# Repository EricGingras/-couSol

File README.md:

# Écou-Terre

**Déscription du projet:** Nous sommes en train de concevoir un module qui peut capter les bruits émis par les vers de terre, offrant ainsi une perspective sur la biodiversité et la santé des sols.  Ceci est le répertoire git de tous les fichiers techniques pour notre projet.

**Déscription technique:** Nous utilisons un microphone électret pour capter le bruit des vers de terre. Ce signal est ensuite amplifié et numérisé pour pouvoir le transmettre dans un ESP-32 en format I2S. Par la suite, ces données I2S sont enregistrées dans une carte SD en format WAV, ce qui permet ensuite de les écouter sur un ordinateur. Il y a aussi un connecteur jack 3,5mm pour l'écoute en temps réelle des vers de terre. Éventuellement, nous souhaitons ajouter un module GPS pouvant indiquer la position géographique de tous les échantillons sonores prélevés. Le module au complet est alimenté par une pile 4.2 volts. Pour le contrôler, nous allons avoir un page web avec un interface pour le démarrage, l'ârret et d'autre fonctions du module.

# Fichiers
> Déscription des fichiers dans le répertoire git.
- **3d_print:** Contient les fichiers pour la seule impression 3d que nous avons fait pour notre projet à date: une base pour le boîtier.
- **Documentation_pieces:** Contient tous les fichiers de documentation pour les pièces principales qui se retrouvent sur le module.
- **Documentation_session5:** Contient des fichiers de la session passée qui servent encore pour notre projet.
- **Fichier_PCB:** Contient tous les fichiers KiCad pour les PCB.
- **Prog_ESP-32:** Contient le code pour l'enregistrement des données I2S qui utilisait ESP-IDF ainsi que le code pour le serveur web qui servira à contrôler le module.

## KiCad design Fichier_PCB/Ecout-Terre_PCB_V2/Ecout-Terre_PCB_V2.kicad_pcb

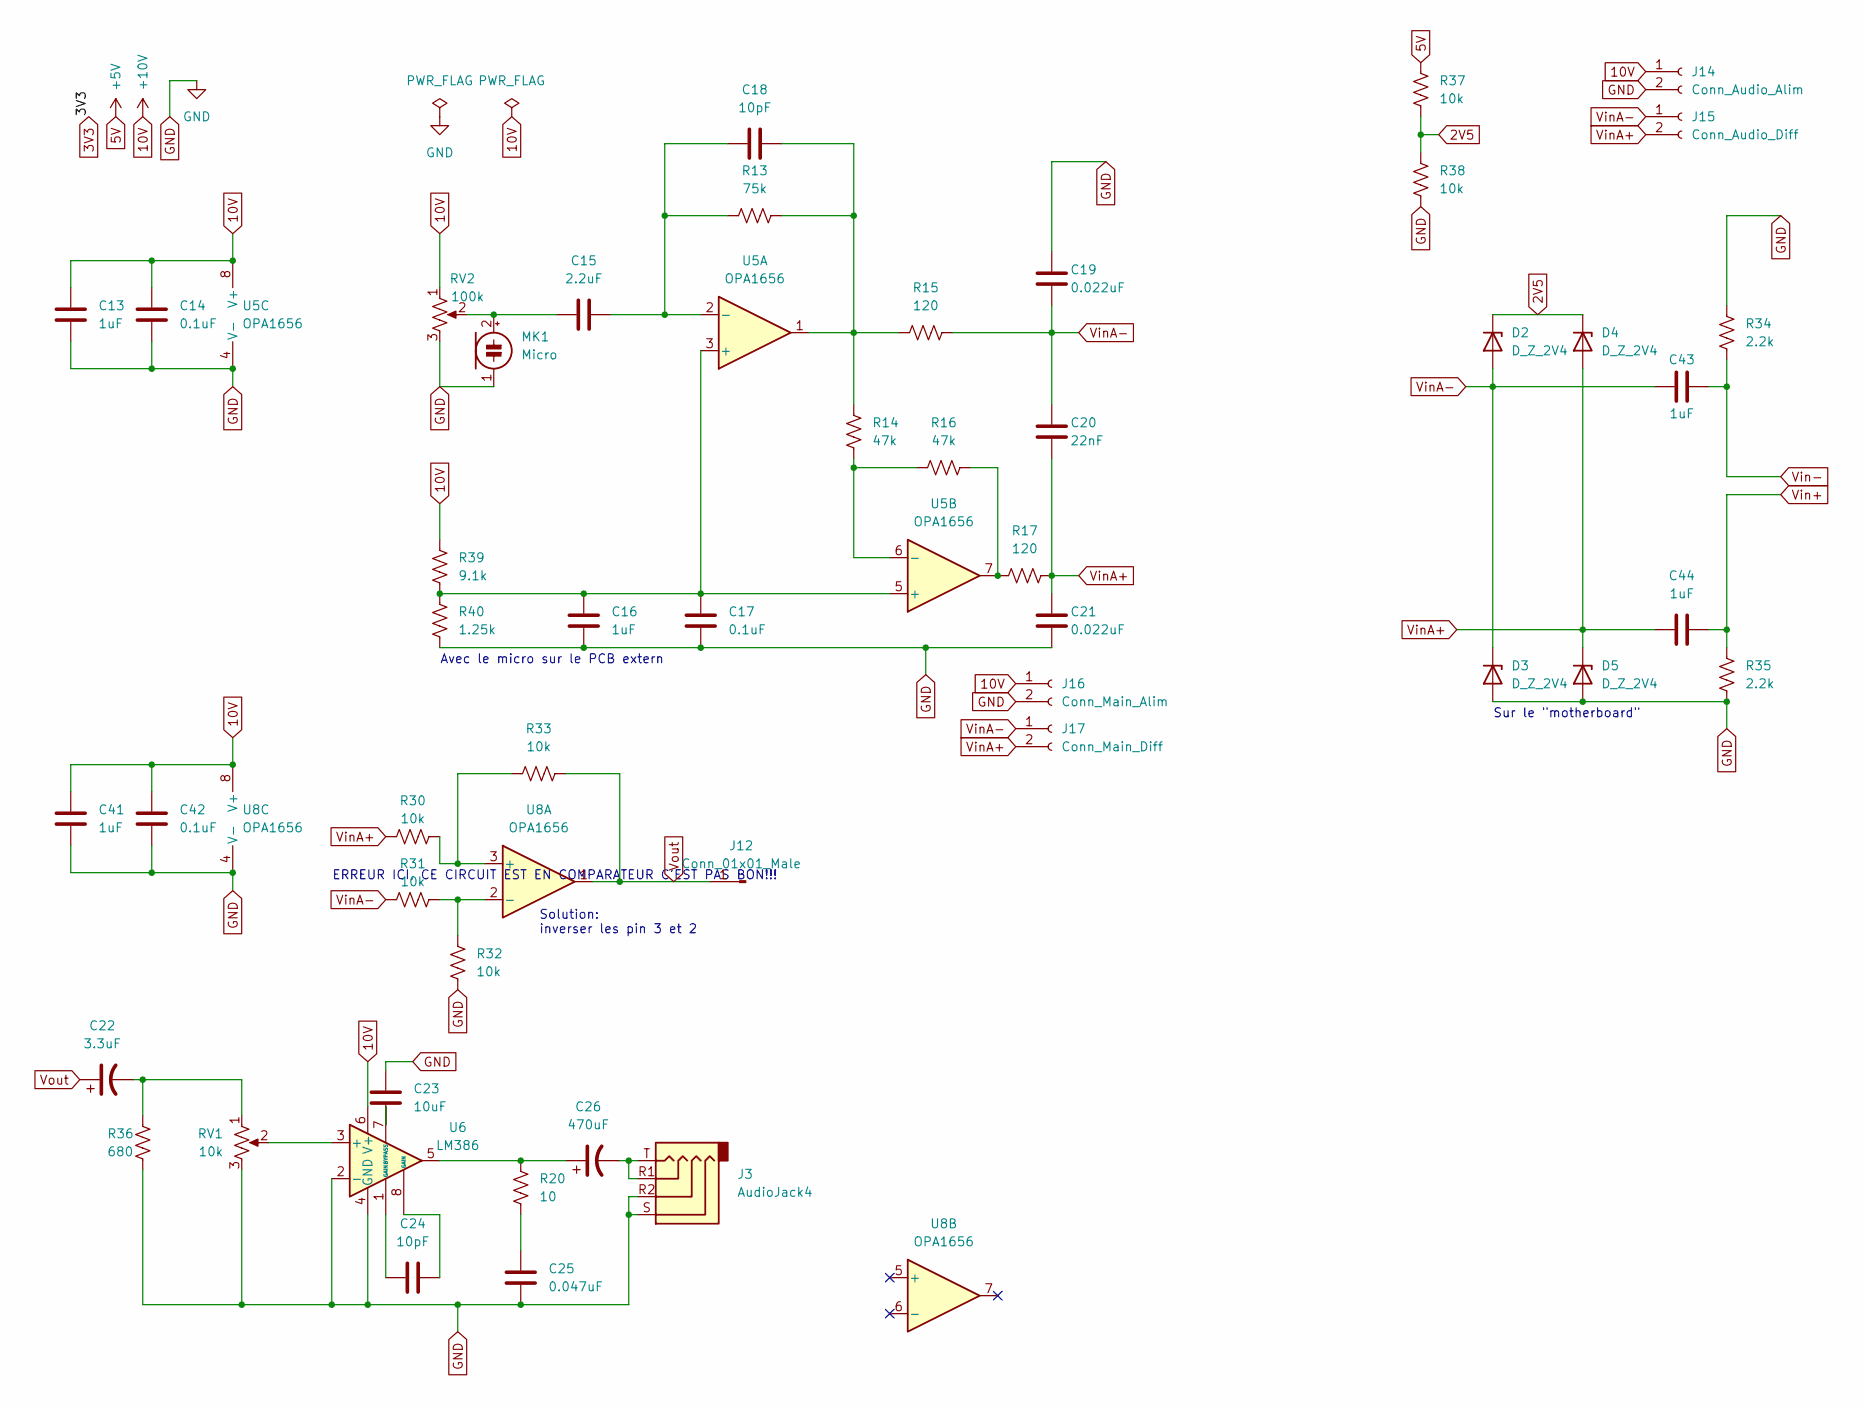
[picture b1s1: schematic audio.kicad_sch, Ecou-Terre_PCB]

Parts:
C13, C16, C41, C43, C44: 1uF; C_0805_2012Metric_Pad1.18x1.45mm_HandSolder
C14, C17, C42: 0.1uF; C_0805_2012Metric_Pad1.18x1.45mm_HandSolder
C15: 2.2uF; C_0805_2012Metric_Pad1.18x1.45mm_HandSolder
C18, C24: 10pF; C_0805_2012Metric_Pad1.18x1.45mm_HandSolder
C19, C21: 0.022uF; C_0805_2012Metric_Pad1.18x1.45mm_HandSolder
C20: 22nF; C_0805_2012Metric_Pad1.18x1.45mm_HandSolder
C22: 3.3uF; C_0805_2012Metric_Pad1.18x1.45mm_HandSolder
C23: 10uF; C_0805_2012Metric_Pad1.18x1.45mm_HandSolder
C25: 0.047uF; C_0805_2012Metric_Pad1.18x1.45mm_HandSolder
C26: 470uF; C_Elec_8x10.2
D2, D3, D4, D5: D_Z_2V4; D_SOD-123
J3: AudioJack4; Jack_3.5mm_CUI_SJ-3524-SMT_Horizontal
J12: Conn_01x01_Male; PinSocket_1x01_P2.54mm_Vertical
J14: Conn_Audio_Alim; SolderWire-0.75sqmm_1x02_P4.8mm_D1.25mm_OD2.3mm
J15: Conn_Audio_Diff; SolderWire-0.75sqmm_1x02_P4.8mm_D1.25mm_OD2.3mm
J16: Conn_Main_Alim; SolderWire-0.75sqmm_1x02_P4.8mm_D1.25mm_OD2.3mm
J17: Conn_Main_Diff; SolderWire-0.75sqmm_1x02_P4.8mm_D1.25mm_OD2.3mm
MK1: Micro; SolderWire-0.1sqmm_1x02_P3.6mm_D0.4mm_OD1mm
R13: 75k; R_0805_2012Metric_Pad1.20x1.40mm_HandSolder
R14, R16: 47k; R_0805_2012Metric_Pad1.20x1.40mm_HandSolder
R15, R17: 120; R_0805_2012Metric_Pad1.20x1.40mm_HandSolder
R20: 10; R_0805_2012Metric_Pad1.20x1.40mm_HandSolder
R30, R31, R32, R33, R37, R38: 10k; R_0805_2012Metric_Pad1.20x1.40mm_HandSolder
R34, R35: 2.2k; R_0805_2012Metric_Pad1.20x1.40mm_HandSolder
R36: 680; R_0805_2012Metric_Pad1.20x1.40mm_HandSolder
R39: 9.1k; R_0805_2012Metric_Pad1.20x1.40mm_HandSolder
R40: 1.25k; R_0805_2012Metric_Pad1.20x1.40mm_HandSolder
RV1: 10k; Potentiometer_Bourns_3386P_Vertical
RV2: 100k; Potentiometer_Bourns_TC33X_Vertical
U5, U8: OPA1656; SOIC-8_3.9x4.9mm_P1.27mm
U6: LM386; SOIC-8_3.9x4.9mm_P1.27mm

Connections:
2V5: D2.1 (K), D4.1 (K), R37.1, R38.2
5V: R37.2; also elsewhere on the board
10V: C13.2, C14.2, C41.2, C42.2, J14.1, J16.1, R39.1, RV2.1, U5.8 (V+), U6.6 (V+), U8.8 (V+); also elsewhere on the board
GND: C13.1, C14.1, C16.1, C17.1, C19.2, C21.1, C23.1, C25.2, C41.1, C42.1, D3.2 (A), D5.2 (A), J3.R2, J3.S, J3.TN, J14.2, J16.2, MK1.1 (-), R32.1, R34.1, R35.2, R36.1, R38.1, R40.2, RV1.3, RV2.3, U5.4 (V-), U6.2 (-), U6.4 (GND), U8.4 (V-); also elsewhere on the board
unnamed: C15.1, MK1.2 (+), RV2.2
unnamed: C15.2, C18.1, R13.1, U5.2 (-)
unnamed: C16.2, C17.2, R39.2, R40.1, U5.3 (+), U5.5 (+)
unnamed: C18.2, R13.2, R14.1, R15.1, U5.1
unnamed: C22.2, R36.2, RV1.1
unnamed: C23.2, U6.7 (BYPASS)
unnamed: C24.1, U6.1 (GAIN)
unnamed: C24.2, U6.8 (GAIN)
unnamed: C25.1, R20.2
unnamed: C26.1, R20.1, U6.5
unnamed: C26.2, J3.R, J3.R1, J3.T
unnamed: R14.2, R16.1, U5.6 (-)
unnamed: R16.2, R17.1, U5.7
unnamed: R30.2, R33.1, U8.3 (+)
unnamed: R31.2, R32.2, U8.2 (-)
unnamed: RV1.2, U6.3 (+)
Vin+: C44.1, R35.1; also elsewhere on the board
Vin-: C43.1, R34.2; also elsewhere on the board
VinA+: C20.1, C21.2, C44.2, D4.2 (A), D5.1 (K), J15.2, J17.2, R17.2, R30.1
VinA-: C19.1, C20.2, C43.2, D2.2 (A), D3.1 (K), J15.1, J17.1, R15.2, R31.1
Vout: C22.1, J12.1, R33.2, U8.1

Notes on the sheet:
Solution: inverser les pin 3 et 2
ERREUR ICI, CE CIRCUIT EST EN COMPARATEUR C'EST PAS BON!!!
Sur le "motherboard"
Avec le micro sur le PCB extern

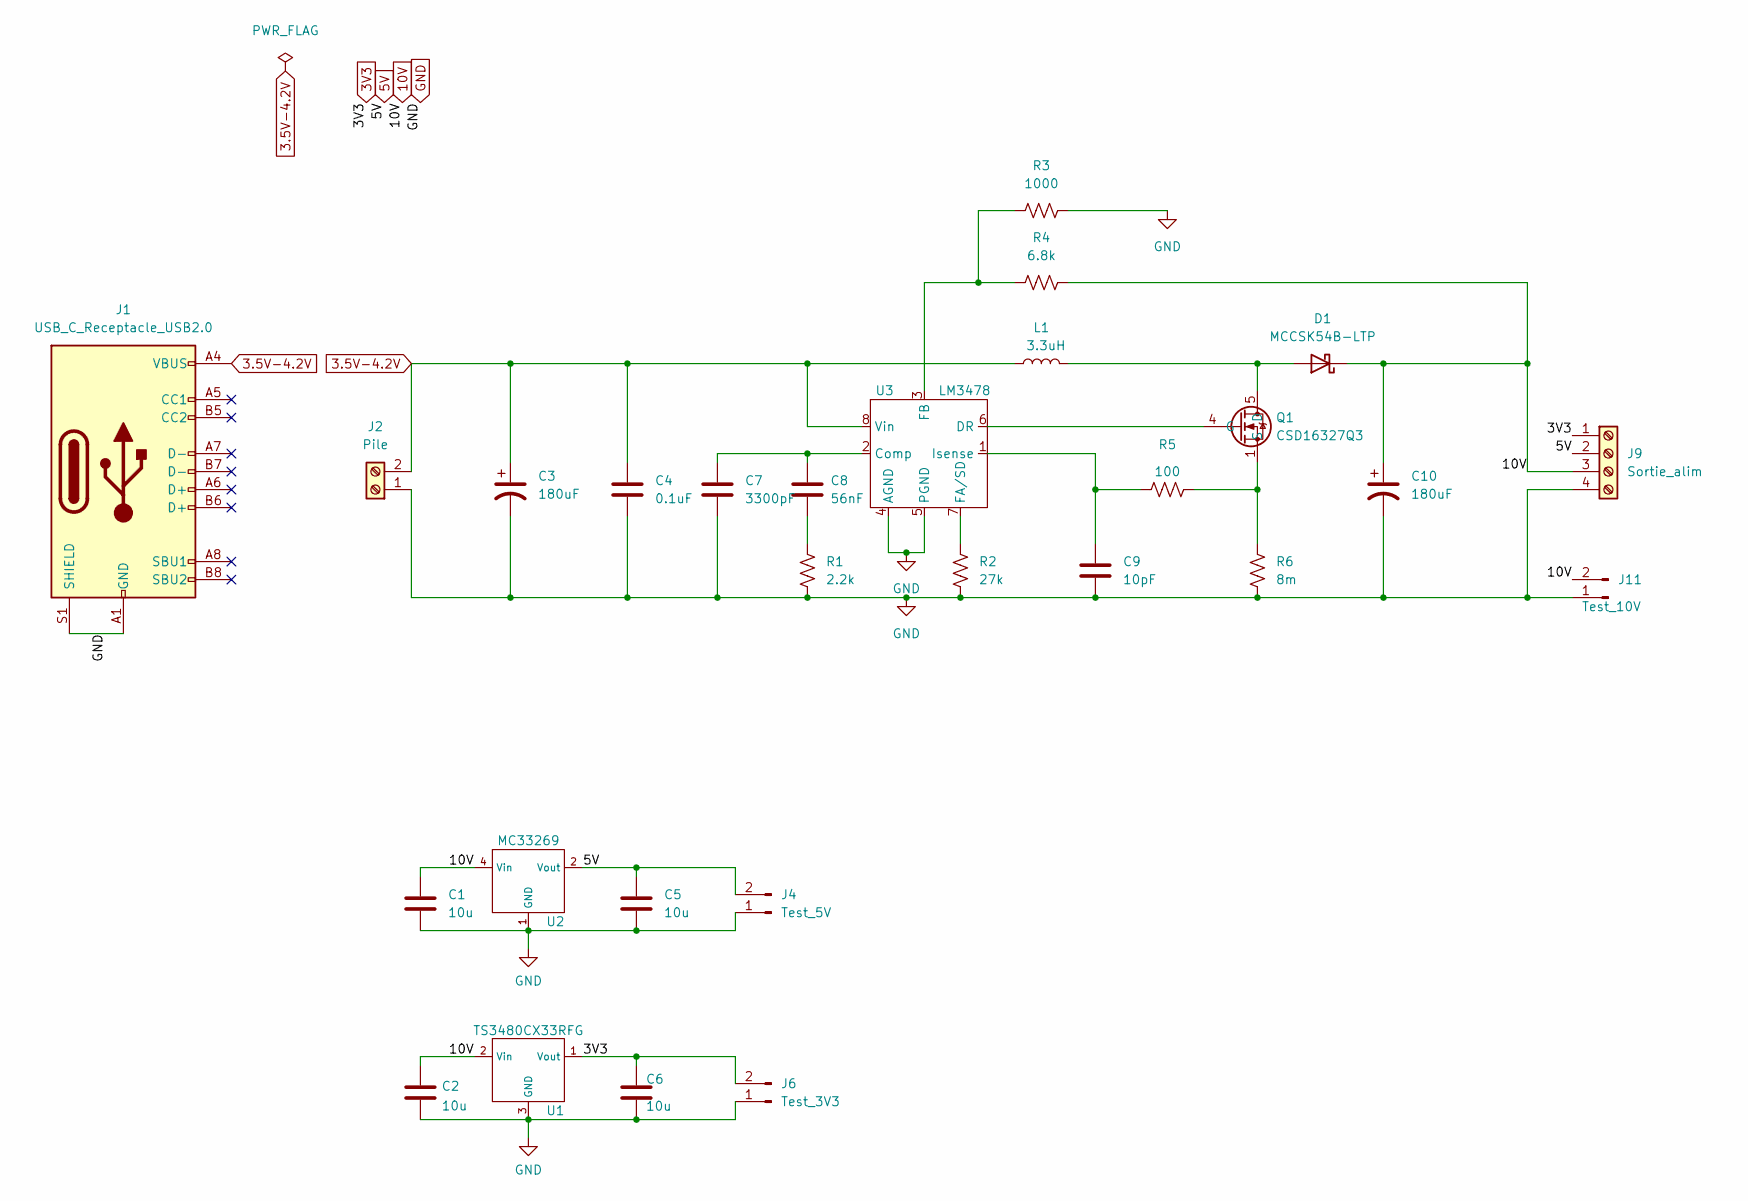
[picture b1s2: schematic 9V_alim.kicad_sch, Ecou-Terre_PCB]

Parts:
C1, C2, C5, C6: 10u; C_0805_2012Metric_Pad1.18x1.45mm_HandSolder
C3, C10: 180uF; CP_Elec_6.3x9.9
C4: 0.1uF; C_0805_2012Metric_Pad1.18x1.45mm_HandSolder
C7: 3300pF; C_0805_2012Metric_Pad1.18x1.45mm_HandSolder
C8: 56nF; C_0504_1310Metric_Pad0.83x1.28mm_HandSolder
C9: 10pF; C_0805_2012Metric_Pad1.18x1.45mm_HandSolder
D1: MCCSK54B-LTP; D_SMB
J1: USB_C_Receptacle_USB2.0; USB_C_Receptacle_HRO_TYPE-C-31-M-12
J2: Pile; TerminalBlock_bornier-2_P5.08mm
J4: Test_5V; PinHeader_1x02_P2.54mm_Vertical
J6: Test_3V3; PinHeader_1x02_P2.54mm_Vertical
J9: Sortie_alim; TerminalBlock_bornier-4_P5.08mm
J11: Test_10V; PinHeader_1x02_P2.54mm_Vertical
L1: 3.3uH; L_Vishay_IHLP-4040
Q1: CSD16327Q3; VSON-8_3.3x3.3mm_P0.65mm_NexFET
R1: 2.2k; R_0805_2012Metric
R2: 27k; R_0805_2012Metric
R3: 1000; R_0805_2012Metric
R4: 6.8k; R_0805_2012Metric
R5: 100; R_0805_2012Metric
R6: 8m; R_0815_2038Metric_Pad1.20x4.05mm_HandSolder
U1: TS3480CX33RFG; SOT-23
U2: MC33269; SO-8_3.9x4.9mm_P1.27mm
U3: LM3478; SOIC-8_3.9x4.9mm_P1.27mm

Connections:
3.5V-4.2V: C3.1, C4.1, J1.A4 (VBUS), J1.A9 (VBUS), J1.B4 (VBUS), J1.B9 (VBUS), J2.2, L1.1, U3.8 (Vin)
3V3: C6.1, J6.2, J9.1, U1.1 (Vout); also elsewhere on the board
5V: C5.1, J4.2, J9.2, U2.2 (Vout), U2.3 (Vout), U2.6 (Vout), U2.7 (Vout); also elsewhere on the board
10V: C1.1, C2.1, C10.1, D1.1 (K), J9.3, J11.2, R4.2, U1.2 (Vin), U2.4 (Vin); also elsewhere on the board
GND: C1.2, C2.2, C3.2, C4.2, C5.2, C6.2, C7.2, C9.2, C10.2, J1.A1 (GND), J1.A12 (GND), J1.B1 (GND), J1.B12 (GND), J1.S1 (SHIELD), J2.1, J4.1, J6.1, J9.4, J11.1, R1.2, R2.2, R3.2, R6.1, U1.3 (GND), U2.1 (GND), U3.4 (AGND), U3.5 (PGND); also elsewhere on the board
unnamed: C7.1, C8.1, U3.2 (Comp)
unnamed: C8.2, R1.1
unnamed: C9.1, R5.1, U3.1 (Isense)
unnamed: D1.2 (A), L1.2, Q1.5 (D)
unnamed: Q1.1 (S), Q1.2 (S), Q1.3 (S), R5.2, R6.2
unnamed: Q1.4 (G), U3.6 (DR)
unnamed: R2.1, U3.7 (FA/SD)
unnamed: R3.1, R4.1, U3.3 (FB)

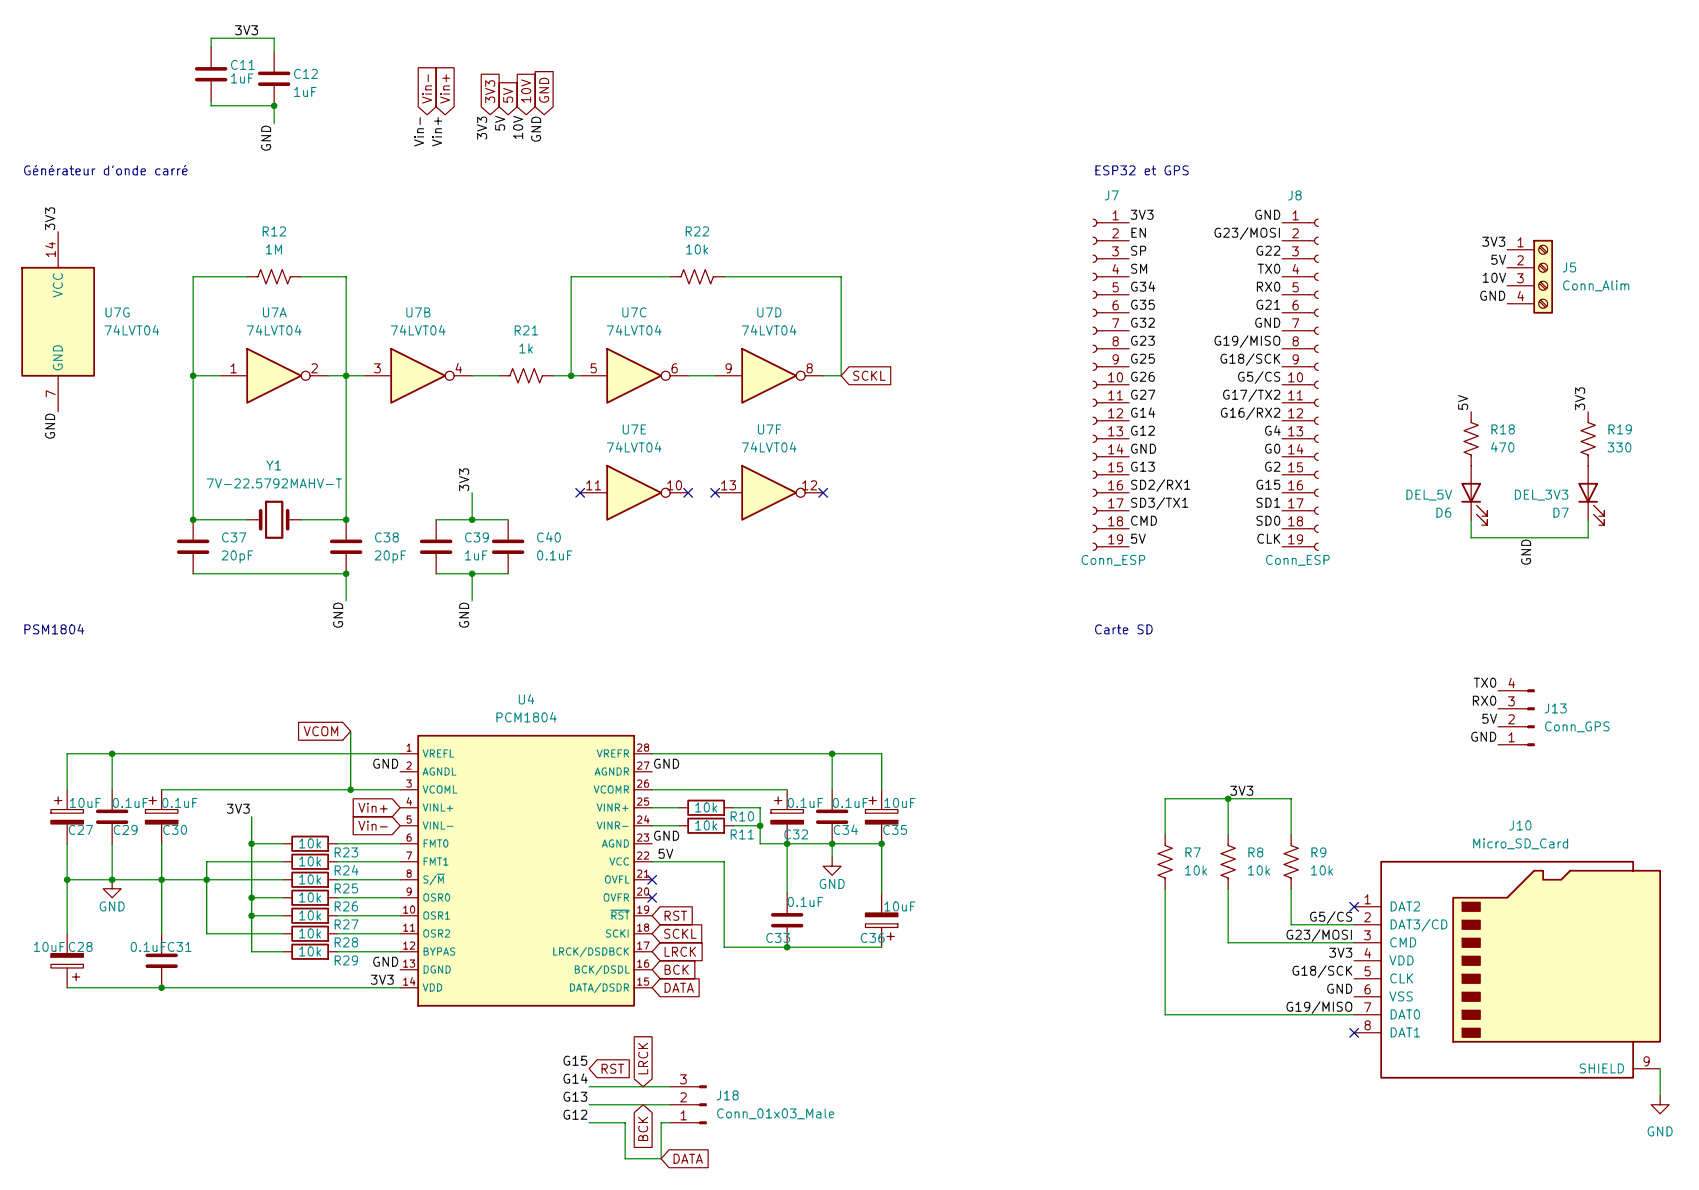
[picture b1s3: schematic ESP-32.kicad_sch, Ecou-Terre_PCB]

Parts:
C11, C12, C39: 1uF; C_0805_2012Metric_Pad1.18x1.45mm_HandSolder
C27, C28, C35, C36: 10uF; C_0805_2012Metric_Pad1.18x1.45mm_HandSolder
C29, C30, C31, C32, C33, C34, C40: 0.1uF; C_0805_2012Metric_Pad1.18x1.45mm_HandSolder
C37, C38: 20pF; C_0805_2012Metric_Pad1.18x1.45mm_HandSolder
D6: DEL_5V; LED_0805_2012Metric_Pad1.15x1.40mm_HandSolder
D7: DEL_3V3; LED_0805_2012Metric_Pad1.15x1.40mm_HandSolder
J5: Conn_Alim; TerminalBlock_bornier-4_P5.08mm
J7, J8: Conn_ESP; PinSocket_1x19_P2.54mm_Vertical
J10: Micro_SD_Card; microSD_HC_Wuerth_693072010801
J13: Conn_GPS; PinSocket_1x04_P2.00mm_Vertical
J18: Conn_01x03_Male; PinHeader_1x03_P2.54mm_Vertical
R7, R8, R9, R10, R11, R22, R23, R24, R25, R26, R27, R28, R29: 10k; R_0805_2012Metric_Pad1.20x1.40mm_HandSolder
R12: 1M; R_0805_2012Metric_Pad1.20x1.40mm_HandSolder
R18: 470; R_0805_2012Metric_Pad1.20x1.40mm_HandSolder
R19: 330; R_0805_2012Metric_Pad1.20x1.40mm_HandSolder
R21: 1k; R_0805_2012Metric_Pad1.20x1.40mm_HandSolder
U4: PCM1804; SSOP-28_5.3x10.2mm_P0.65mm
U7: 74LVT04; SOIC-14_3.9x8.7mm_P1.27mm
Y1: 7V-22.5792MAHV-T; Crystal_SMD_3225-4Pin_3.2x2.5mm

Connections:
3V3: C11.1, C12.1, C28.1, C31.1, C39.1, C40.1, J5.1, J7.1, J10.4 (VDD), R7.1, R8.1, R9.1, R19.1, R23.1, R26.1, R27.1, R29.1, U4.14 (VDD), U7.14 (VCC); also elsewhere on the board
5V: C33.1, C36.1, J5.2, J7.19, J13.2, R18.1, U4.22 (VCC); also elsewhere on the board
10V: J5.3; also elsewhere on the board
/ESP-32/CLK: J8.19
/ESP-32/CMD: J7.18
/ESP-32/EN: J7.2
/ESP-32/G0: J8.14
/ESP-32/G2: J8.15
/ESP-32/G4: J8.13
/ESP-32/G5/CS: J8.10, J10.2 (DAT3/CD), R9.2
/ESP-32/G16/RX2: J8.12
/ESP-32/G17/TX2: J8.11
/ESP-32/G18/SCK: J8.9, J10.5 (CLK)
/ESP-32/G19/MISO: J8.8, J10.7 (DAT0), R7.2
/ESP-32/G21: J8.6
/ESP-32/G22: J8.3
/ESP-32/G23: J7.8
/ESP-32/G23/MOSI: J8.2, J10.3 (CMD), R8.2
/ESP-32/G25: J7.9
/ESP-32/G26: J7.10
/ESP-32/G27: J7.11
/ESP-32/G32: J7.7
/ESP-32/G34: J7.5
/ESP-32/G35: J7.6
/ESP-32/RX0: J8.5, J13.3
/ESP-32/SD0: J8.18
/ESP-32/SD1: J8.17
/ESP-32/SD2/RX1: J7.16
/ESP-32/SD3/TX1: J7.17
/ESP-32/SM: J7.4
/ESP-32/SP: J7.3
/ESP-32/TX0: J8.4, J13.4
BCK: J7.15, J18.2, U4.16 (BCK/DSDL)
DATA: J7.13, J18.1, U4.15 (DATA/DSDR)
GND: C11.2, C12.2, C27.2, C28.2, C29.1, C30.2, C31.2, C32.2, C33.2, C34.1, C35.2, C36.2, C37.2, C38.2, C39.2, C40.2, D6.1 (K), D7.1 (K), J5.4, J7.14, J8.1, J8.7, J10.6 (VSS), J10.9 (SHIELD), J13.1, R10.2, R11.2, R24.1, R25.1, R28.1, U4.2 (AGNDL), U4.13 (DGND), U4.23 (AGND), U4.27 (AGNDR), U7.7 (GND); also elsewhere on the board
LRCK: J7.12, J18.3, U4.17 (LRCK/DSDBCK)
unnamed: C27.1, C29.2, U4.1 (VREFL)
unnamed: C32.1, U4.26 (VCOMR)
unnamed: C34.2, C35.1, U4.28 (VREFR)
unnamed: C37.1, R12.1, U7.1, Y1.1
unnamed: C38.1, R12.2, U7.2, U7.3, Y1.2, Y1.3
unnamed: D6.2 (A), R18.2
unnamed: D7.2 (A), R19.2
unnamed: R10.1, U4.25 (VINR+)
unnamed: R11.1, U4.24 (VINR-)
unnamed: R21.1, U7.4
unnamed: R21.2, R22.1, U7.5
unnamed: R23.2, U4.6 (FMT0)
unnamed: R24.2, U4.7 (FMT1)
unnamed: R25.2, U4.8 (S/~M)
unnamed: R26.2, U4.9 (OSR0)
unnamed: R27.2, U4.10 (OSR1)
unnamed: R28.2, U4.11 (OSR2)
unnamed: R29.2, U4.12 (BYPAS)
unnamed: U7.6, U7.9
RST: J8.16, U4.19 (~RST)
SCKL: R22.2, U4.18 (SCKI), U7.8
VCOM: C30.1, U4.3 (VCOML)
Vin+: U4.4 (VINL+); also elsewhere on the board
Vin-: U4.5 (VINL-); also elsewhere on the board

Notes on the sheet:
ESP32 et GPS
Générateur d'onde carré
PSM1804
Carte SD

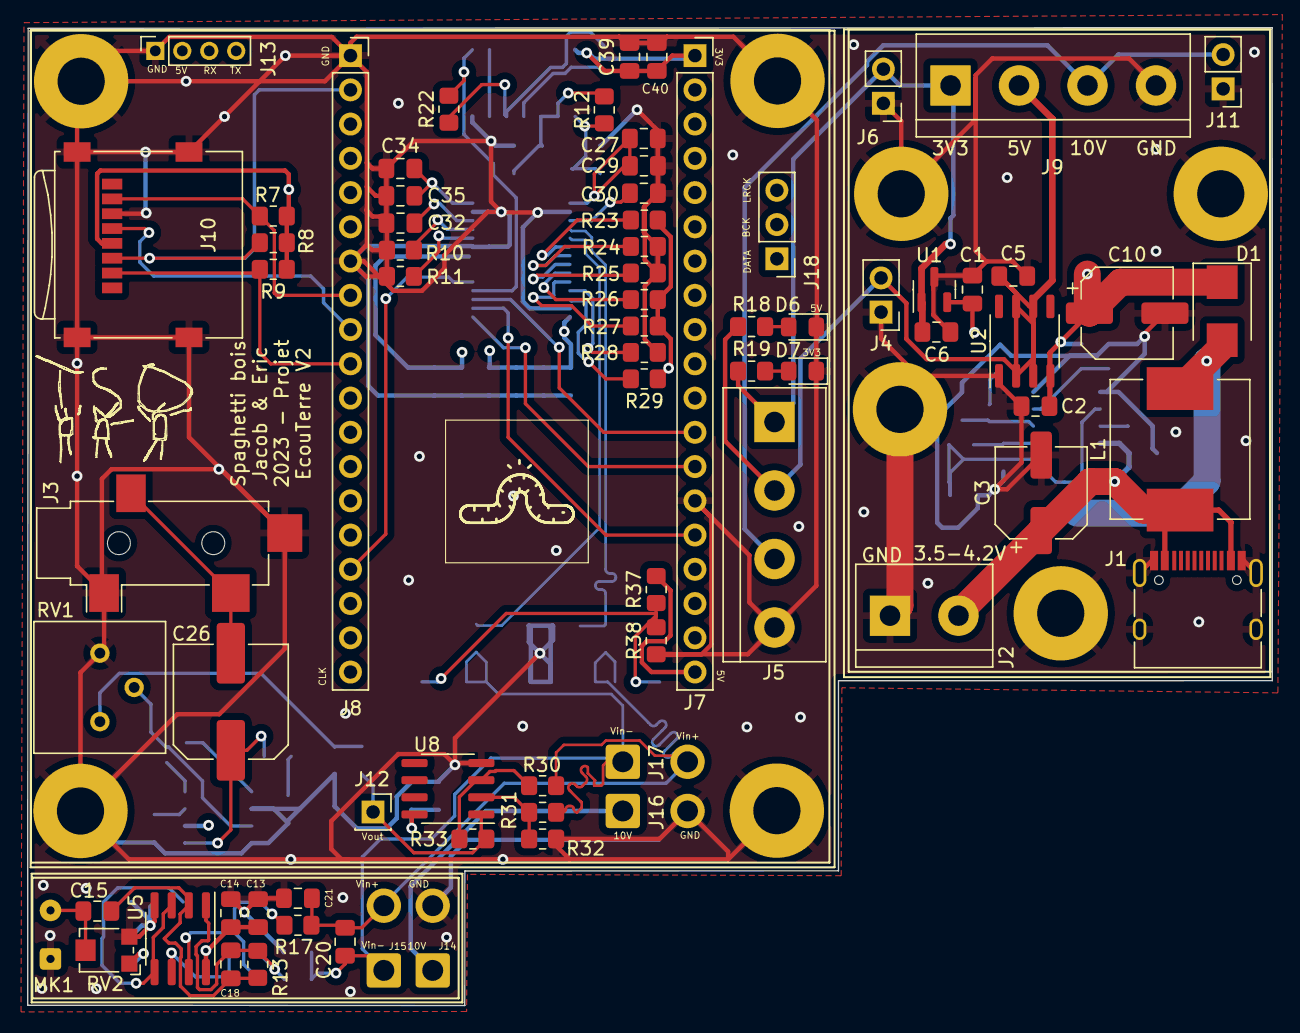
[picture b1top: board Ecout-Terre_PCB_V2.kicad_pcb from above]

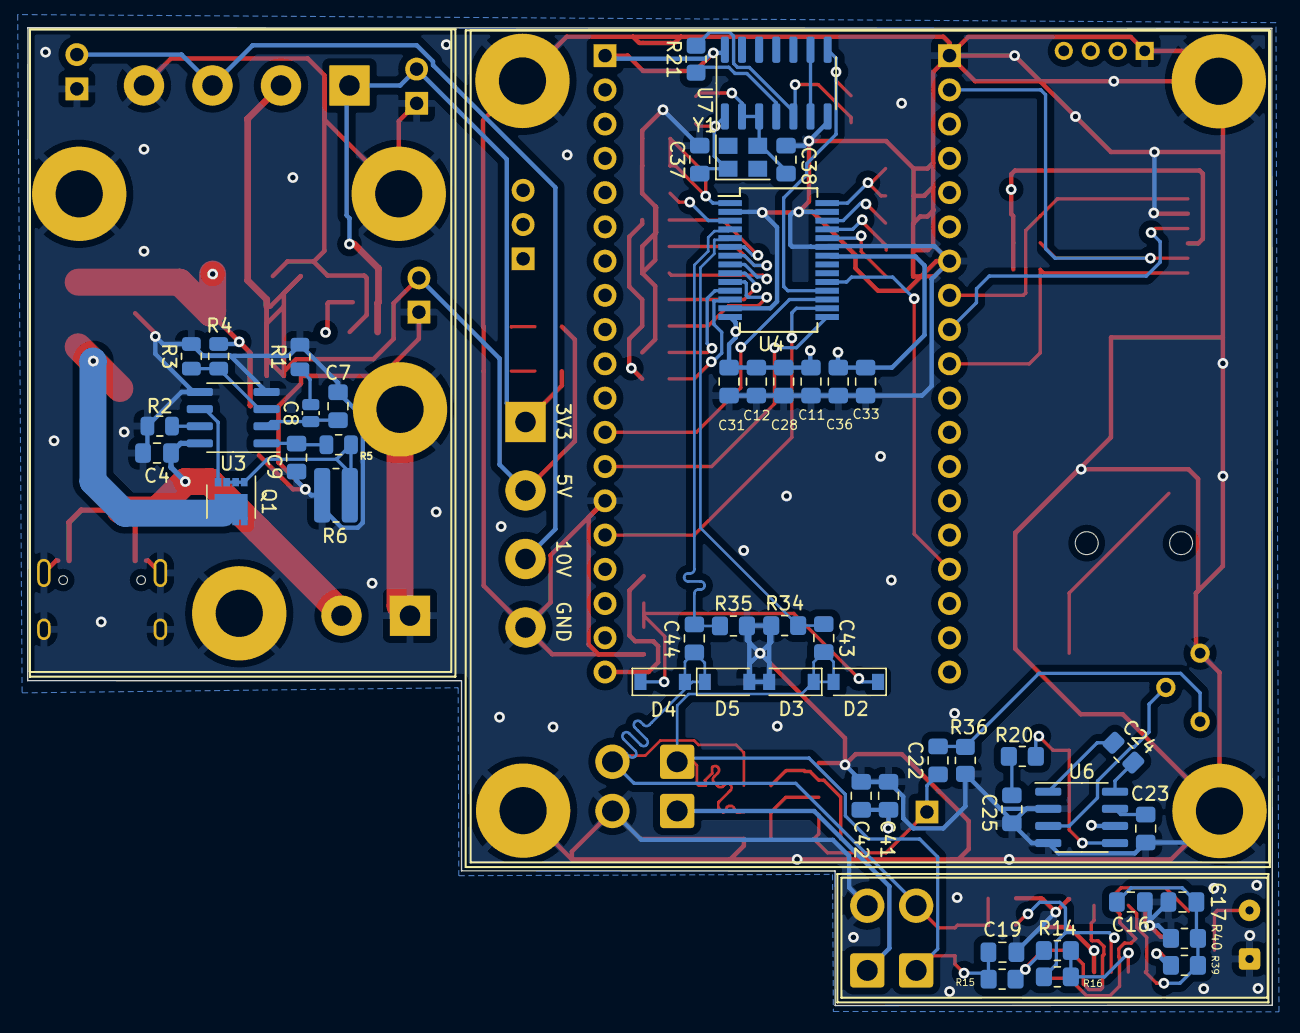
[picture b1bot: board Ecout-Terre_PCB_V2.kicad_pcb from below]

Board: 4 copper layers, 92.3 x 72.5 mm, 123 parts (49 on the bottom side), 66 nets.

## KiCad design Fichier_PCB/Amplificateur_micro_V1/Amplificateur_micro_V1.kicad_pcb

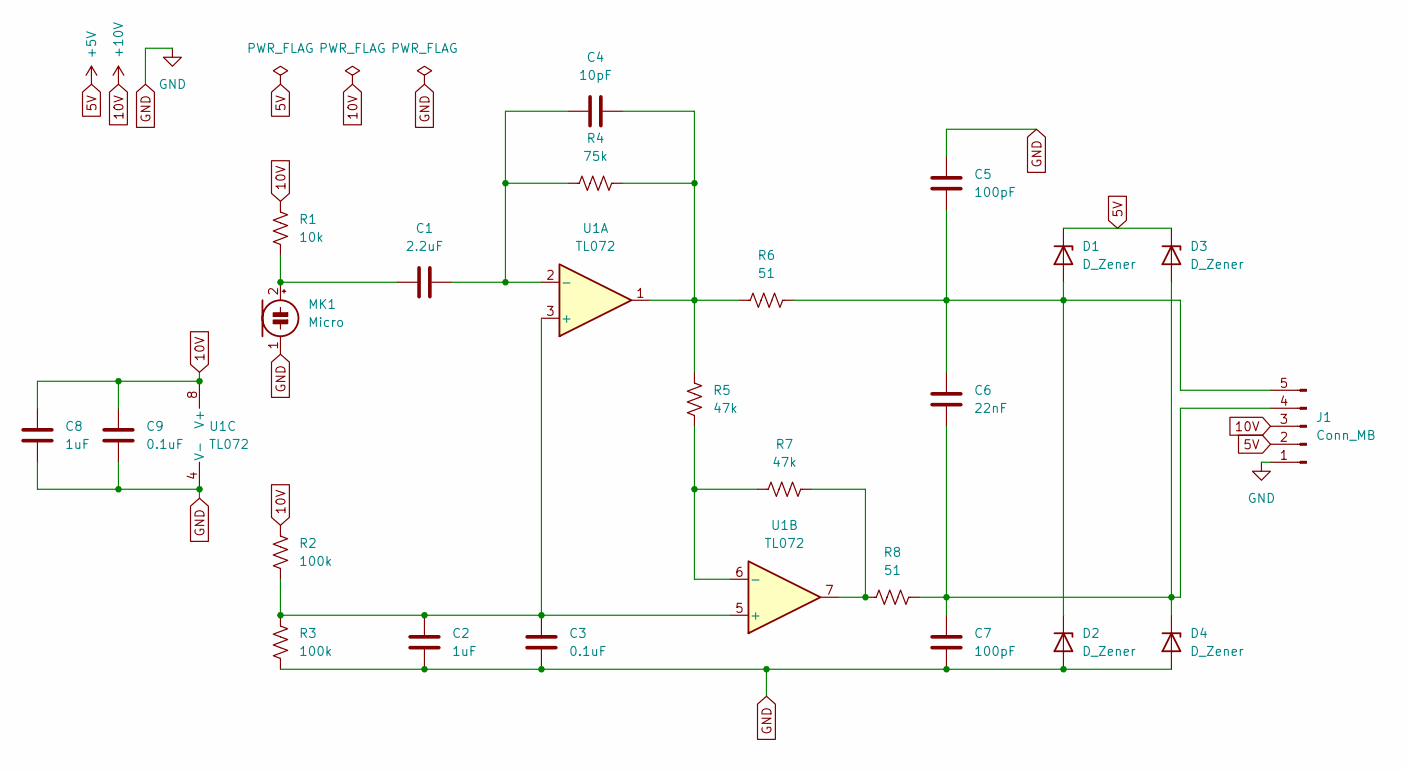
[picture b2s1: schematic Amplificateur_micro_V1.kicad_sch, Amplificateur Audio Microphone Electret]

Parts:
C1: 2.2uF; C_0805_2012Metric_Pad1.18x1.45mm_HandSolder
C2, C8: 1uF; C_0805_2012Metric_Pad1.18x1.45mm_HandSolder
C3, C9: 0.1uF; C_0805_2012Metric_Pad1.18x1.45mm_HandSolder
C4: 10pF; C_0805_2012Metric_Pad1.18x1.45mm_HandSolder
C5, C7: 100pF; C_0805_2012Metric_Pad1.18x1.45mm_HandSolder
C6: 22nF; C_0805_2012Metric_Pad1.18x1.45mm_HandSolder
D1, D2, D3, D4: D_Zener; D_SOD-123
J1: Conn_MB; PinSocket_1x05_P2.00mm_Vertical
MK1: Micro; PinSocket_1x02_P2.00mm_Vertical
R1: 10k; R_0805_2012Metric_Pad1.20x1.40mm_HandSolder
R2, R3: 100k; R_0805_2012Metric_Pad1.20x1.40mm_HandSolder
R4: 75k; R_0805_2012Metric_Pad1.20x1.40mm_HandSolder
R5, R7: 47k; R_0805_2012Metric_Pad1.20x1.40mm_HandSolder
R6, R8: 51; R_0805_2012Metric_Pad1.20x1.40mm_HandSolder
U1: TL072; SOT-23-8_Handsoldering

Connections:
5V: D1.1 (K), D3.1 (K), J1.2
10V: C8.2, C9.2, J1.3, R1.1, R2.1, U1.8 (V+)
GND: C2.1, C3.1, C5.2, C7.1, C8.1, C9.1, D2.2 (A), D4.2 (A), J1.1, MK1.1 (-), R3.2, U1.4 (V-)
unnamed: C1.1, MK1.2 (+), R1.2
unnamed: C1.2, C4.1, R4.1, U1.2 (-)
unnamed: C2.2, C3.2, R2.2, R3.1, U1.3 (+), U1.5 (+)
unnamed: C4.2, R4.2, R5.1, R6.1, U1.1
unnamed: C5.1, C6.2, D1.2 (A), D2.1 (K), J1.5, R6.2
unnamed: C6.1, C7.2, D3.2 (A), D4.1 (K), J1.4, R8.2
unnamed: R5.2, R7.1, U1.6 (-)
unnamed: R7.2, R8.1, U1.7

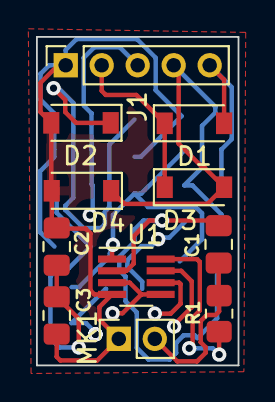
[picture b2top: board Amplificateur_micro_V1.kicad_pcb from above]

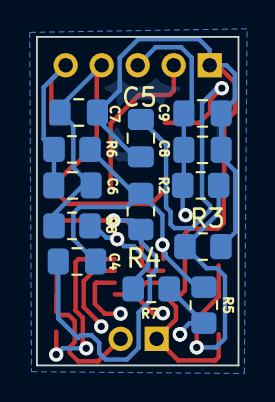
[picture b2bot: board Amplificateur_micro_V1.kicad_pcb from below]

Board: 4 copper layers, 11.2 x 18.2 mm, 24 parts (13 on the bottom side), 11 nets.

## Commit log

2023-01-19 fichier créer
2023-01-19 Ajout du code pour interfaceOrdi
2023-01-19 commit de documentation
2023-01-19 documentation session 1
2023-01-19 Test
2023-01-19 document session 1 pcb
2023-01-19 Ajout du dossier de l'interface ordi
2023-01-26 Terminer PCB ampli audio
2023-01-26 Excel de liste de pièce
2023-01-30 Ajout des descriptions de fichiers dans le README
2023-02-09 Ajout du fichier arduino pour le pcm1804
2023-02-09 Upload du fichier kicad pour le pcm1804
2023-02-09 kicad pour pcm1804 version 1 fini
2023-02-09 ajout du fichier pcm1804.pdf
2023-02-09 ajout du pdf pour le pcm1804
2023-02-09 ajout du fichier pdf pour le pcm1804
2023-02-13 Ajout du code python pour le sauvegarde et l'affichage du fichier wav
2023-02-14 PCB_version1
2023-03-14 Kicad, PA et site web
2023-03-20 Trace pcb
2023-04-03 Ajout de la version plus récente du code pour la lecture I2S qui sauvegarde à la carte SD
2023-04-03 Envoie de code et correction PCB
2023-04-03 Ajout de pièces 3d
    Pièce qui va dans la bas du boîtier. Le PCB sera vissé dessus
2023-04-03 Création Readme
    Création readme pour le répertoire Prog_esp-32
2023-04-03 Modification du Readme
    Ajout de description du code ainsi que des instructions d'utilisation
2023-04-03 Ajout du schéma synoptique pour le readme
2023-04-04 Delete Prog_Esp-32/ESP_IDF_WEB_SERVER/.devcontainer directory
    Fichier non nécessaire au fonctionnement du code. Je l'enlève pour rendre le tout plus facile à utiliser et à lire.
2023-04-04 Delete Prog_Esp-32/ESP_IDF_WEB_SERVER/.vscode directory
    Fichier non nécessaire au fonctionnement du code. Je l'enlève pour rendre le tout plus facile à utiliser et à lire.
2023-04-04 Delete Prog_Esp-32/ESP_IDF_WEB_SERVER/build directory
    Fichier non nécessaire au fonctionnement du code. Je l'enlève pour rendre le tout plus facile à utiliser et à lire.
2023-04-04 changement de png à jpg pour le schéma synoptique
2023-04-04 Mauvais fichier de lecture I2S remplacé avec le bon
2023-04-17 Répertoire + fichier zip kicad
    Fichier .zip kicad pour envoyer à JLCPCB
    Nouveau répertoire pour créer procédure de setup
2023-04-17 Création du fichier README.md
    je fais juste rajouter le fichier. je vais le changer dans pas long
2023-04-17 pas besoin
2023-04-17 Ajout du fichier le plus récent d'enregistrement I2S
2023-05-01 Ajout du code le plus récent pour l'I2S
2023-05-01 Clarification du schéma pcb
2023-05-01 Ajout de génération de fichier
    Crée un fichier enregistrement'N' où N est égal au nombre d'enregistrement. Besoin de faire une gestion des doublons
2023-05-01 Gestion DEL, gestion fichier doublon, correction schéma électrique
    PIN 23 à côté de la PIN 25 est en fait la PIN 33.
    Gestion de DEL pour qu'elle flash au quart de seconde.
    Gestion de doublon de fichier afin que l'application crée un nouveau fichier selon le nombre de fichier déjà existant. (aucun écrasement)
2023-05-05 Suppression du déscription du répertoire Arduino
2023-05-05 Suppression du répertoire Prog_Arduino
2023-05-05 Réécriture du readme
2023-05-05 ajout d'une description pour i2s_record_final
2023-05-05 Suppression du répertoire InterfaceOrdi
2023-05-05 ajout de commentaire
2023-05-06 Ajout de commentaires au code I2S
